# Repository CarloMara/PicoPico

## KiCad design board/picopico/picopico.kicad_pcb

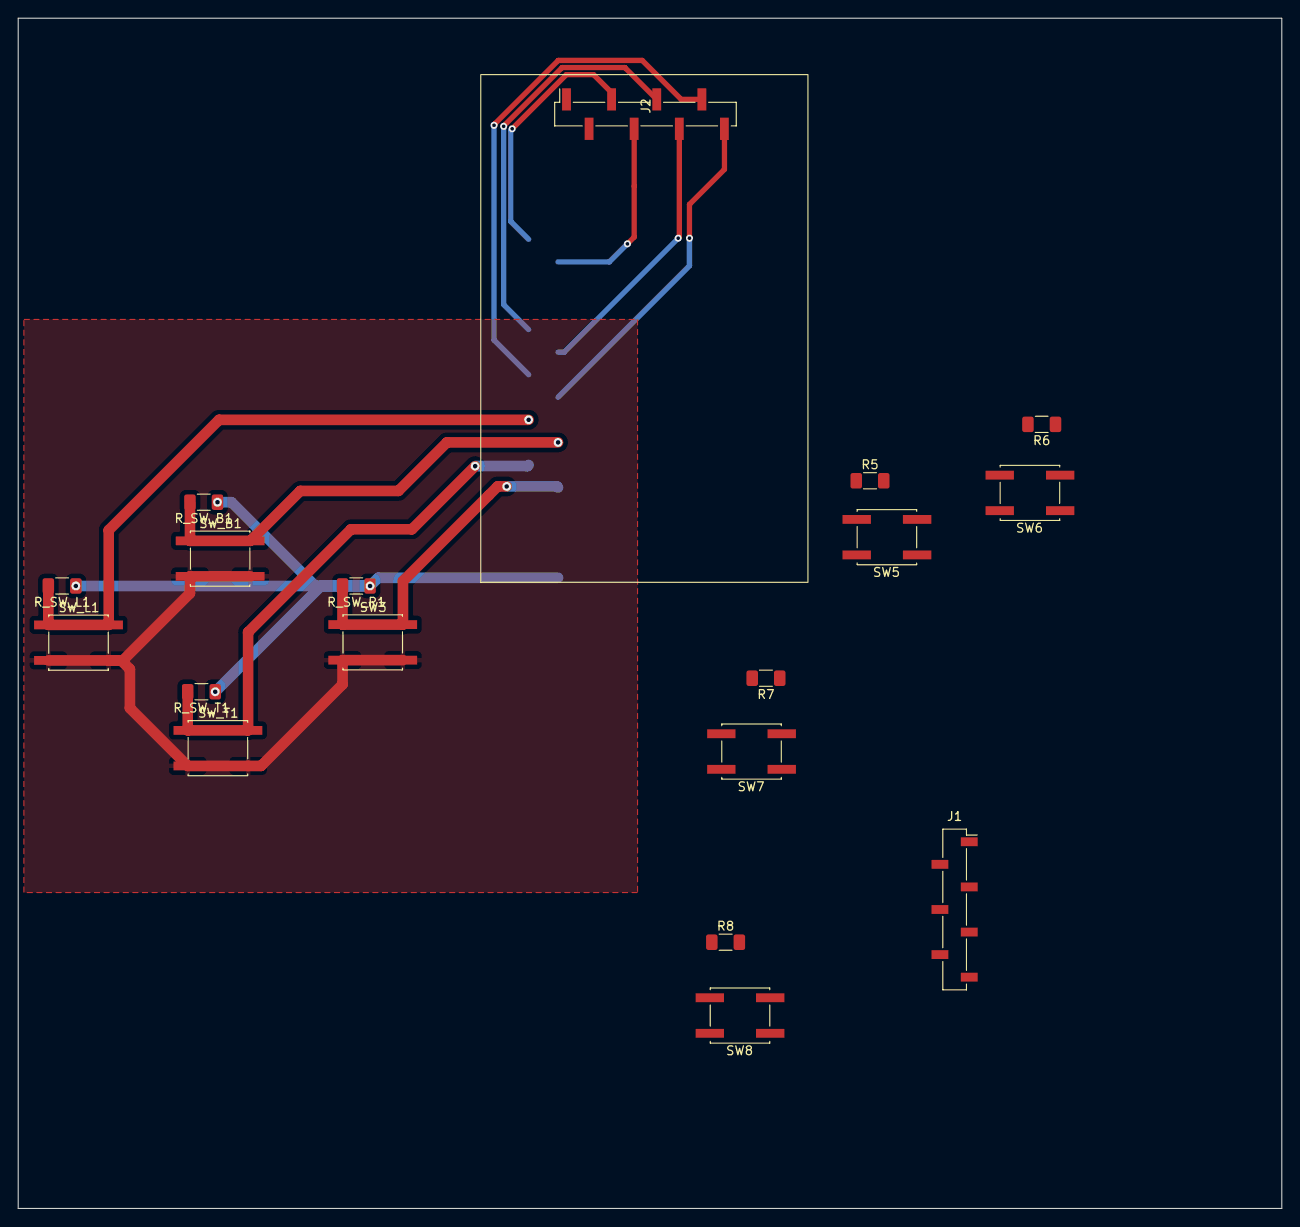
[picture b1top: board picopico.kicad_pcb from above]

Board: 2 copper layers, 142.2 x 134.0 mm, 19 parts (1 on the bottom side), 19 nets.

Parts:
J1: audio_chip; PinSocket_1x07_P2.54mm_Vertical_SMD_Pin1Right
J2: display; 1.77 display
R5, R6, R7, R8: R; R_1206_3216Metric_Pad1.30x1.75mm_HandSolder
R_SW_B1: 10K; R_1206_3216Metric_Pad1.30x1.75mm_HandSolder
R_SW_L1: 10K; R_1206_3216Metric_Pad1.30x1.75mm_HandSolder
R_SW_R1: 10K; R_1206_3216Metric_Pad1.30x1.75mm_HandSolder
R_SW_T1: 10K; R_1206_3216Metric_Pad1.30x1.75mm_HandSolder
SW3, SW5, SW6, SW7, SW8: SW_Push; SW_SPST_EVQQ2
SW_B1: SW_Push; SW_SPST_EVQQ2
SW_L1: SW_Push; SW_SPST_EVQQ2
SW_T1: SW_Push; SW_SPST_EVQQ2
U1: DollaTekESP32; DollaTecESP32

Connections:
+3V3: J1.7, J2.2, R5.2, R6.2, R7.2, R8.2, R_SW_B1.1, R_SW_L1.1, R_SW_R1.1, R_SW_T1.1, U1.18 (3.3v)
/BCLK: J1.2, U1.11 (27)
/CS: J2.7, U1.27 (18)
/DC/RS: J2.6, U1.28 (19)
/DIN: J1.3, U1.10 (26)
/LED/BL: J2.8, U1.26 (5)
/LRC: J1.1, U1.12 (14)
/RESET: J2.5, U1.29 (21)
/SCK: J2.3, U1.33 (23)
/SDA: J2.4, U1.32 (22)
/SW_B: R_SW_B1.2, SW_B1.1, U1.24 (0)
/SW_L: R_SW_L1.2, SW_L1.1, U1.25 (4)
/SW_R: R_SW_R1.2, SW3.1, U1.22 (15)
/SW_T: R_SW_T1.2, SW_T1.1, U1.23 (2)
GND: J1.4, J1.5, J1.6, J2.1, SW3.2, SW5.1, SW6.1, SW7.1, SW8.1, SW_B1.2, SW_L1.2, SW_T1.2
unnamed: R5.1, SW5.2
unnamed: R6.1, SW6.2
unnamed: R7.1, SW7.2
unnamed: R8.1, SW8.2

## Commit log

2022-10-17 routing buttons
